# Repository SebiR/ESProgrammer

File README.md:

# ESProgrammer
A simple USB programming interface for ESP8266/ESP32

## Features
* Automatic Reset/GPIO0
* TagConnect interface for custom devices
* Direct connector for ESP-01 modules

# Pinout and TagConnect
**RX of Programmer to RX of ESP and TX to TX**
(Which is a bit confusing to be honest)

The TagConnect connector follows my own standard which I've created for my devices using an ESP8266.

The device should utilize this pinout:

Whereas TXD goes to the TXD of the ESP8266 and RXD goes to the RXD of the ESP.

# Jumper
## Automatic
The two "Automatic" jumpers allow for an automatic trigger of the Reset and GPIO0 line during programming like on NodeMCU boards and Tasmotizer.
Manual resetting and triggering GPIO0 will always be possible with the push buttons.

## 3V3/5V
The other jumper near the TagConnect allows for a selection of the power supply voltage of the TagConnect. When my device has an LDO and 5V power supply, VCC will be set to 5V and the VCC pin on the device goes to the 5V input of the board.

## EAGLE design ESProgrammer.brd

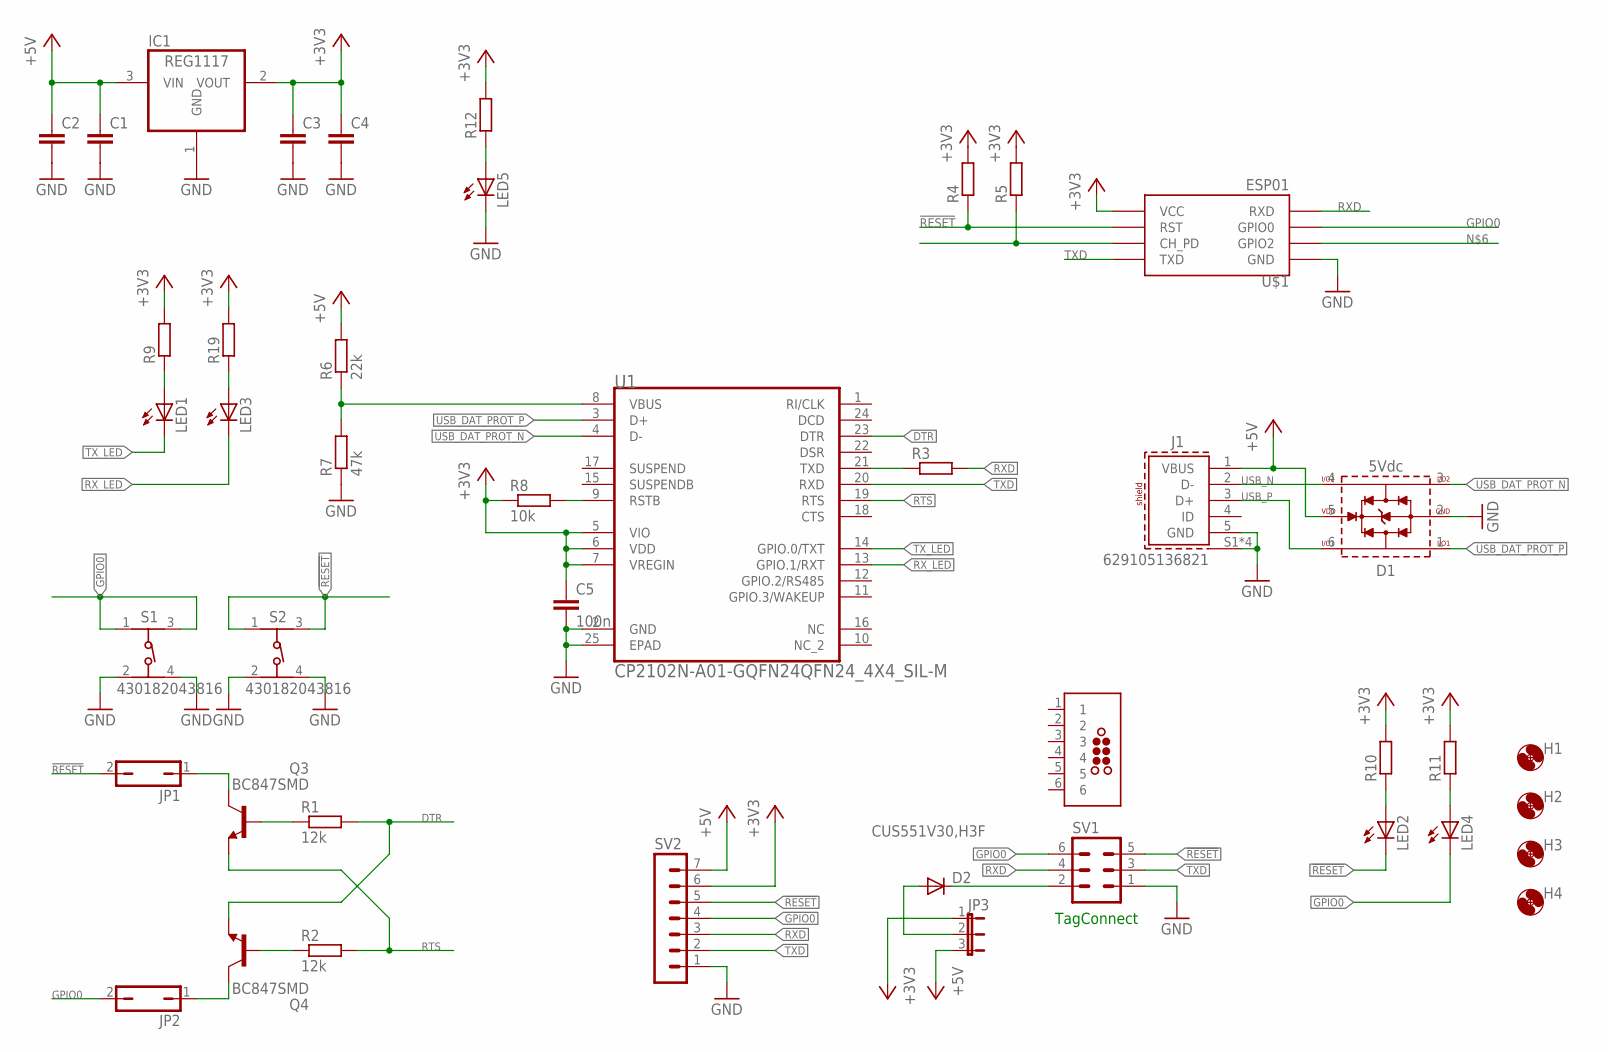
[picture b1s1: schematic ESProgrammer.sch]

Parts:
C1, C2, C3, C4: C-EUC0603; C0603
C5: 100n; C0603
D1: 5Vdc; WE-TVS_SOT23-6L
D2: CUS551V30,H3F; SOD323-R
H1, H2, H3, H4: MOUNT-HOLE3.2; 3,2
IC1: REG1117; SOT223
J1: 629105136821
J2: TC2030-MCP-NL
JP1, JP2: JP1Q; JP1
JP3: JP2E; JP2
LED1, LED2, LED3, LED4, LED5: LEDCHIP-LED0603; CHIP-LED0603
Q3, Q4: BC847SMD; SOT23
R1, R2: 12k; R0603
R3, R4, R5, R9, R10, R11, R12, R19: R-EU_R0603; R0603
R6: 22k; R0603
R7: 47k; R0603
R8: 10k; R0603
S1, S2: 430182043816
SV1: ML6
SV2: MA07-1
U1: CP2102N-A01-GQFN24QFN24_4X4_SIL-M; QFN24_4X4_SIL-M
U$1: ESP01

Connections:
2: J2.2
3: J2.3
!RESET: JP1.2, LED2.C, R4.1, S2.1, S2.3, SV1.5, SV2.5, U$1.RST
+3V3: C3.1, C4.1, C5.1, IC1.2 (VOUT), JP3.1, R4.2, R5.2, R8.1, R9.2, R10.2, R11.2, R12.2, R19.2, SV2.6, U1.5 (VIO), U1.6 (VDD), U1.7 (VREGIN), U$1.VCC
+5V: C1.1, C2.1, D1.5 (VDD), IC1.3 (VIN), J1.1 (VBUS), JP3.3, R6.2, SV2.7
DTR: Q4.2 (E), R1.2, U1.23 (DTR)
GND: C1.2, C2.2, C3.2, C4.2, C5.2, D1.2 (GND), IC1.1 (GND), J1.5 (GND), J1.S1 (SHIELD), J1.S2 (SHIELD), J1.S3 (SHIELD), J1.S4 (SHIELD), LED5.C, R7.1, S1.2, S1.4, S2.2, S2.4, SV1.1, SV2.1, U1.2 (GND), U1.25 (EPAD), U$1.GND
GPIO0: JP2.2, LED4.C, S1.1, S1.3, SV1.6, SV2.4, U$1.GPIO0
unnamed: Q3.1 (B), R1.1
unnamed: Q4.1 (B), R2.1
unnamed: JP1.1, Q3.3 (C)
unnamed: JP2.1, Q4.3 (C)
unnamed: R3.1, U1.21 (TXD)
unnamed: R5.1, U$1.CH_PD
unnamed: LED1.A, R9.1
unnamed: LED2.A, R10.1
unnamed: R6.1, R7.2, U1.8 (VBUS)
unnamed: R8.2, U1.9 (RSTB)
unnamed: LED4.A, R11.1
unnamed: LED5.A, R12.1
unnamed: D2.A, JP3.2
unnamed: D2.C, SV1.2
unnamed: LED3.A, R19.1
RTS: Q3.2 (E), R2.2, U1.19 (RTS)
RXD: R3.2, SV1.4, SV2.3, U$1.RX (RXD)
RX_LED: LED3.C, U1.13 (GPIO.1/RXT)
TXD: SV1.3, SV2.2, U1.20 (RXD), U$1.TX (TXD)
TX_LED: LED1.C, U1.14 (GPIO.0/TXT)
USB_DAT_PROT_N: D1.3 (I/O2), U1.4 (D-)
USB_DAT_PROT_P: D1.1 (I/O1), U1.3 (D+)
USB_N: D1.4 (I/O4), J1.2 (D-)
USB_P: D1.6 (I/O3), J1.3 (D+)

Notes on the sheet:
TagConnect

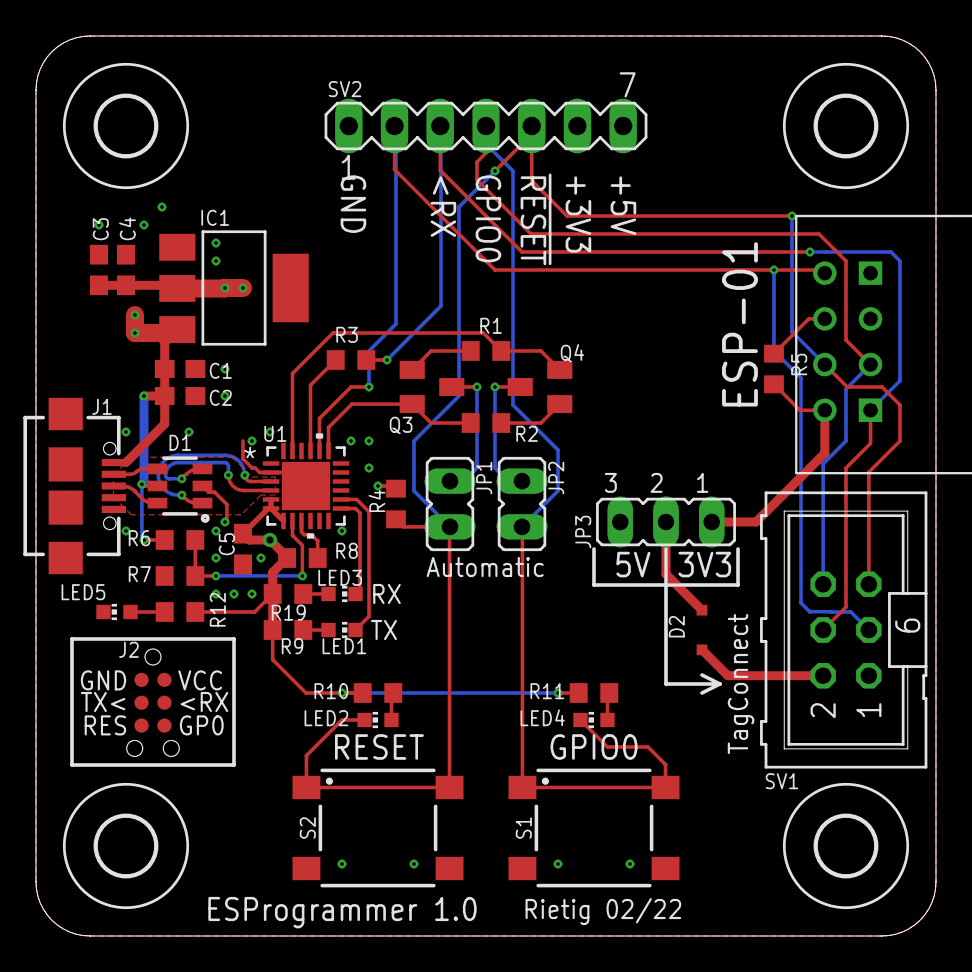
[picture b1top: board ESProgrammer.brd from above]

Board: 4 copper layers, 50.0 x 50.0 mm, 43 parts (0 on the bottom side), 30 nets.

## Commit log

2023-02-25 added photo of the device
2023-02-26 * Updated documentation * Added GERBER and Schematic * Cleaned up the Schematics
2023-02-26 * Updated Documentation * Cleaned up schematics * Added schematic PDF * Added Gerber files

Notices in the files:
parts and their libraries:
Eagle_WR-USB: Copyright: Würth Elektronik
tag-connect: ©2009 ROFA.cz - modified and updated by Robert Darlington ‹rdarlington@gmail.com›
COPYRIGHT: Copyright (C) 2021 Ultra Librarian. All rights reserved.
